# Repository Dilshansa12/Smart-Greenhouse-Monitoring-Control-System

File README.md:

# Smart-Greenhouse-Monitoring-Control-System
The AgroGuard system is an open-source, ESP32 based solution designed for precision agriculture  and automated greenhouse management. It  integrates multiple environmental sensors with a  dual-channel relay board, allowing for real-time  monitoring and automated control of irrigation  and ventilation systems. this is product design product.

## 📖 Table of Contents
- [Overview](#overview)
- [Key Features](#key-features)
- [Hardware Components](#hardware-components)
- [Monitored Parameters](#monitored-parameters)
- [Operating Modes](#operating-modes)
- [Mobile Application](#mobile-application)
- [Safety & Maintenance](#safety--maintenance)

---

## 🚀 Overview
AgroGuard allows users to monitor critical environmental data and control greenhouse equipment remotely via a mobile application. It ensures optimal growing conditions by automatically managing water pumps, fans, and grow lights based on sensor feedback.

## ✨ Key Features
* **Wireless Connectivity:** Integrated Wi-Fi module for seamless cloud integration and remote access.
* **Real-Time Monitoring:** Continuous tracking of temperature, humidity, soil moisture, light, gas levels, and water tank levels.
* **Dual Control Modes:** Supports both **Auto** (Sensor-based) and **Manual** (App-based) control.
* **Smart Alerts:** Instant notifications via Mobile App and Buzzer for critical events (e.g., Low water, Gas leak).
* **Power Control:** Onboard 5V relays to switch AC/DC loads like pumps and fans.
* **Mobile app** controll all equipments.

---

## 🛠 Hardware Components
The system is built using the following components:

* **Main Controller:** ESP32 Development Board
* **Sensors:**
    * Temperature & Humidity Sensor (e.g., DHT11/DHT22)
    * Soil Moisture Sensor
    * Light Intensity Sensor (LDR/BH1750)
    * Gas Sensor (e.g., MQ Series)
    * Water Level Monitoring Circuit
* **Actuators:**
    * 2-Channel 5V Relay Module
    * Buzzer (for local alarms)
* **Power Supply:** Recommended DC source for ESP32 and Relays.

---

## 📊 Monitored Parameters
All data is visualized in real-time on the AgroGuard mobile app:

| Parameter | Unit | Description |
| :--- | :---: | :--- |
| **Temperature** | °C | Ambient air temperature |
| **Humidity** | % | Relative air humidity |
| **Soil Moisture** | % | Moisture content in the soil |
| **Light Intensity** | - | Current light levels |
| **Gas Concentration** | - | Detection of harmful gases/smoke |
| **Water Tank Level** | % | Water availability in the reservoir |

---

## ⚙️ Operating Modes

### 1. Auto Mode 🤖
In this mode, AgroGuard automatically makes decisions based on preset thresholds:
* **Irrigation:** If `Soil Moisture < Threshold` → **Pump ON** 💧
* **Ventilation:** If `Temperature > Threshold` → **Fan ON** ❄️
* **Lighting:** If `Light Intensity < Threshold` → **Grow Light ON** 💡

### 2. Manual Mode 📱
Users can override automation and manually toggle devices (Pumps, Fans, Lights) using the Android/iOS mobile application.

---

## 🚨 Alerts & Notifications
The system ensures safety by generating alerts for:
* ⚠️ **Low Water Tank Level**
* ⚠️ **High Gas Concentration**
* ⚠️ **Abnormal Temperature or Humidity**

*Alerts are delivered via **Mobile Push Notifications** and a local **Buzzer**.*

---

## 🛡 Safety & Maintenance

### Safety Instructions
* ❌ **Do not** expose the main controller PCB to water.
* 🔌 Always disconnect power before performing maintenance.
* ⚡ Use only recommended power supplies.
* 🔒 Ensure all sensor connections are secure.

### Maintenance
* Clean sensors periodically to ensure accuracy.
* Inspect wiring connections regularly.
* Ensure stable Wi-Fi connectivity for remote monitoring.

---

## 📝 License
This project is open-source. Feel free to contribute or modify it for your needs.

---
*Created for the AgroGuard Project (Version 1.0)*

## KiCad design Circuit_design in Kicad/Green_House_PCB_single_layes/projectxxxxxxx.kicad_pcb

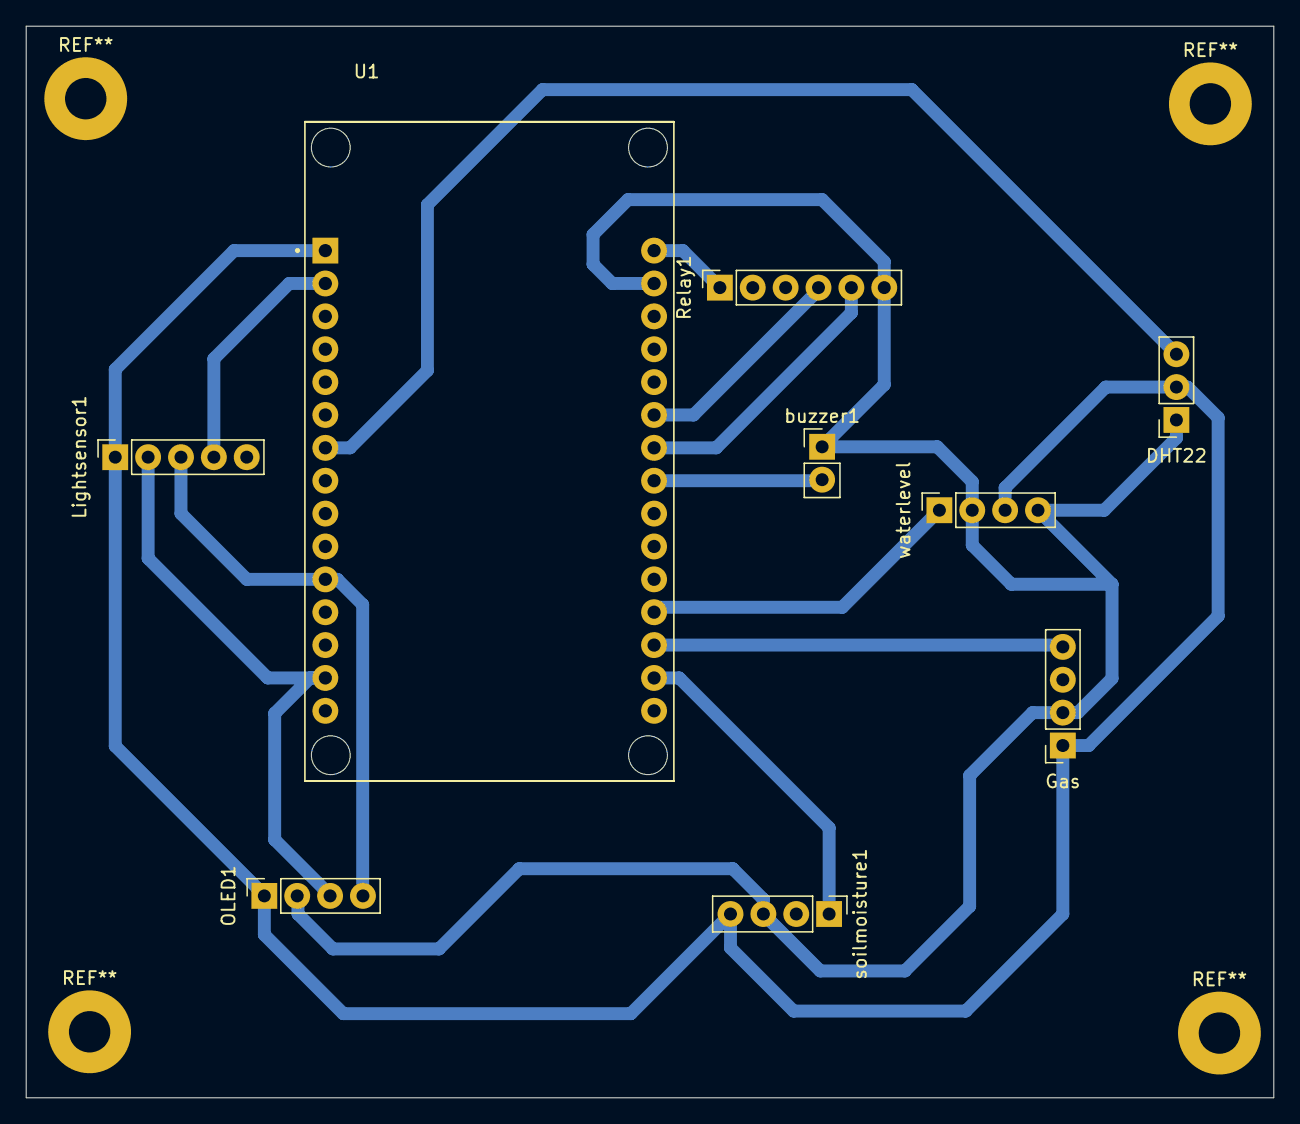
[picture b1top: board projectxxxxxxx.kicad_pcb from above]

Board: 2 copper layers, 96.4 x 82.8 mm, 9 parts (0 on the bottom side), 12 nets.

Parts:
DHT22: Conn_01x03; PinSocket_1x03_P2.54mm_Vertical
Gas: Conn_01x04; PinSocket_1x04_P2.54mm_Vertical
Lightsensor1: Conn_01x05; PinSocket_1x05_P2.54mm_Vertical
OLED1: Conn_01x04; PinSocket_1x04_P2.54mm_Vertical
Relay1: Conn_01x06; PinSocket_1x06_P2.54mm_Vertical
U1: ESP32-DEVKIT-V1; MODULE_ESP32_DEVKIT_V1
buzzer1: Conn_01x02; PinHeader_1x02_P2.54mm_Vertical
soilmoisture1: Conn_01x04; PinHeader_1x04_P2.54mm_Vertical
waterlevel: Conn_01x04; PinSocket_1x04_P2.54mm_Vertical

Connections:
GND: DHT22.1, Gas.2, Lightsensor1.4, OLED1.2, Relay1.6, U1.2 (GND), U1.29 (GND), buzzer1.1, soilmoisture1.3, waterlevel.2, waterlevel.4
unnamed: DHT22.3, U1.7 (TX2)
unnamed: Gas.4, U1.18 (VN)
unnamed: U1.19 (D34), waterlevel.1
unnamed: Lightsensor1.2, OLED1.3, U1.14 (D22)
unnamed: Lightsensor1.3, OLED1.4, U1.11 (D21)
unnamed: Relay1.1, U1.30 (VIN)
unnamed: Relay1.4, U1.25 (D27)
unnamed: Relay1.5, U1.24 (D26)
unnamed: U1.23 (D25), buzzer1.2
unnamed: U1.17 (VP), soilmoisture1.1
VCC: DHT22.2, Gas.1, Lightsensor1.1, OLED1.1, U1.1 (3V3), soilmoisture1.4, waterlevel.3

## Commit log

2026-01-12 Enhance README with detailed project information
    Expanded the README to include detailed sections on features, hardware components, monitored parameters, operating modes, alerts, safety instructions, and maintenance.
2026-01-12 Update README with mobile app control information
    Added a line about mobile app control for equipment.
2026-01-12 Add KiCad circuit design and schematic files
    This commit includes the complete hardware design for the AgroGuard system. It features the schematic diagrams for the ESP32-based main controller, sensor interfaces (BH1750, Soil Moisture Sensor, DH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
2026-01-12 Add product photos and mobile app screenshots
    Uploaded high-quality images of the final hardware assembly and screenshots of the mobile application interface. These assets visualize the system architecture, UI layout, and the physical enclosure 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
2026-01-12 source code in esp32 programming
    Added the core firmware for the ESP32 microcontroller. This code handles data acquisition from environmental sensors (Temperature, Humidity, Soil Moisture), manages the dual-channel relay control for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
2026-01-12 source code in mobile app
    Included the complete source code for the mobile dashboard application. This app allows users to monitor real-time sensor data, receive alerts for critical events, and toggle between Auto/Manual cont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
